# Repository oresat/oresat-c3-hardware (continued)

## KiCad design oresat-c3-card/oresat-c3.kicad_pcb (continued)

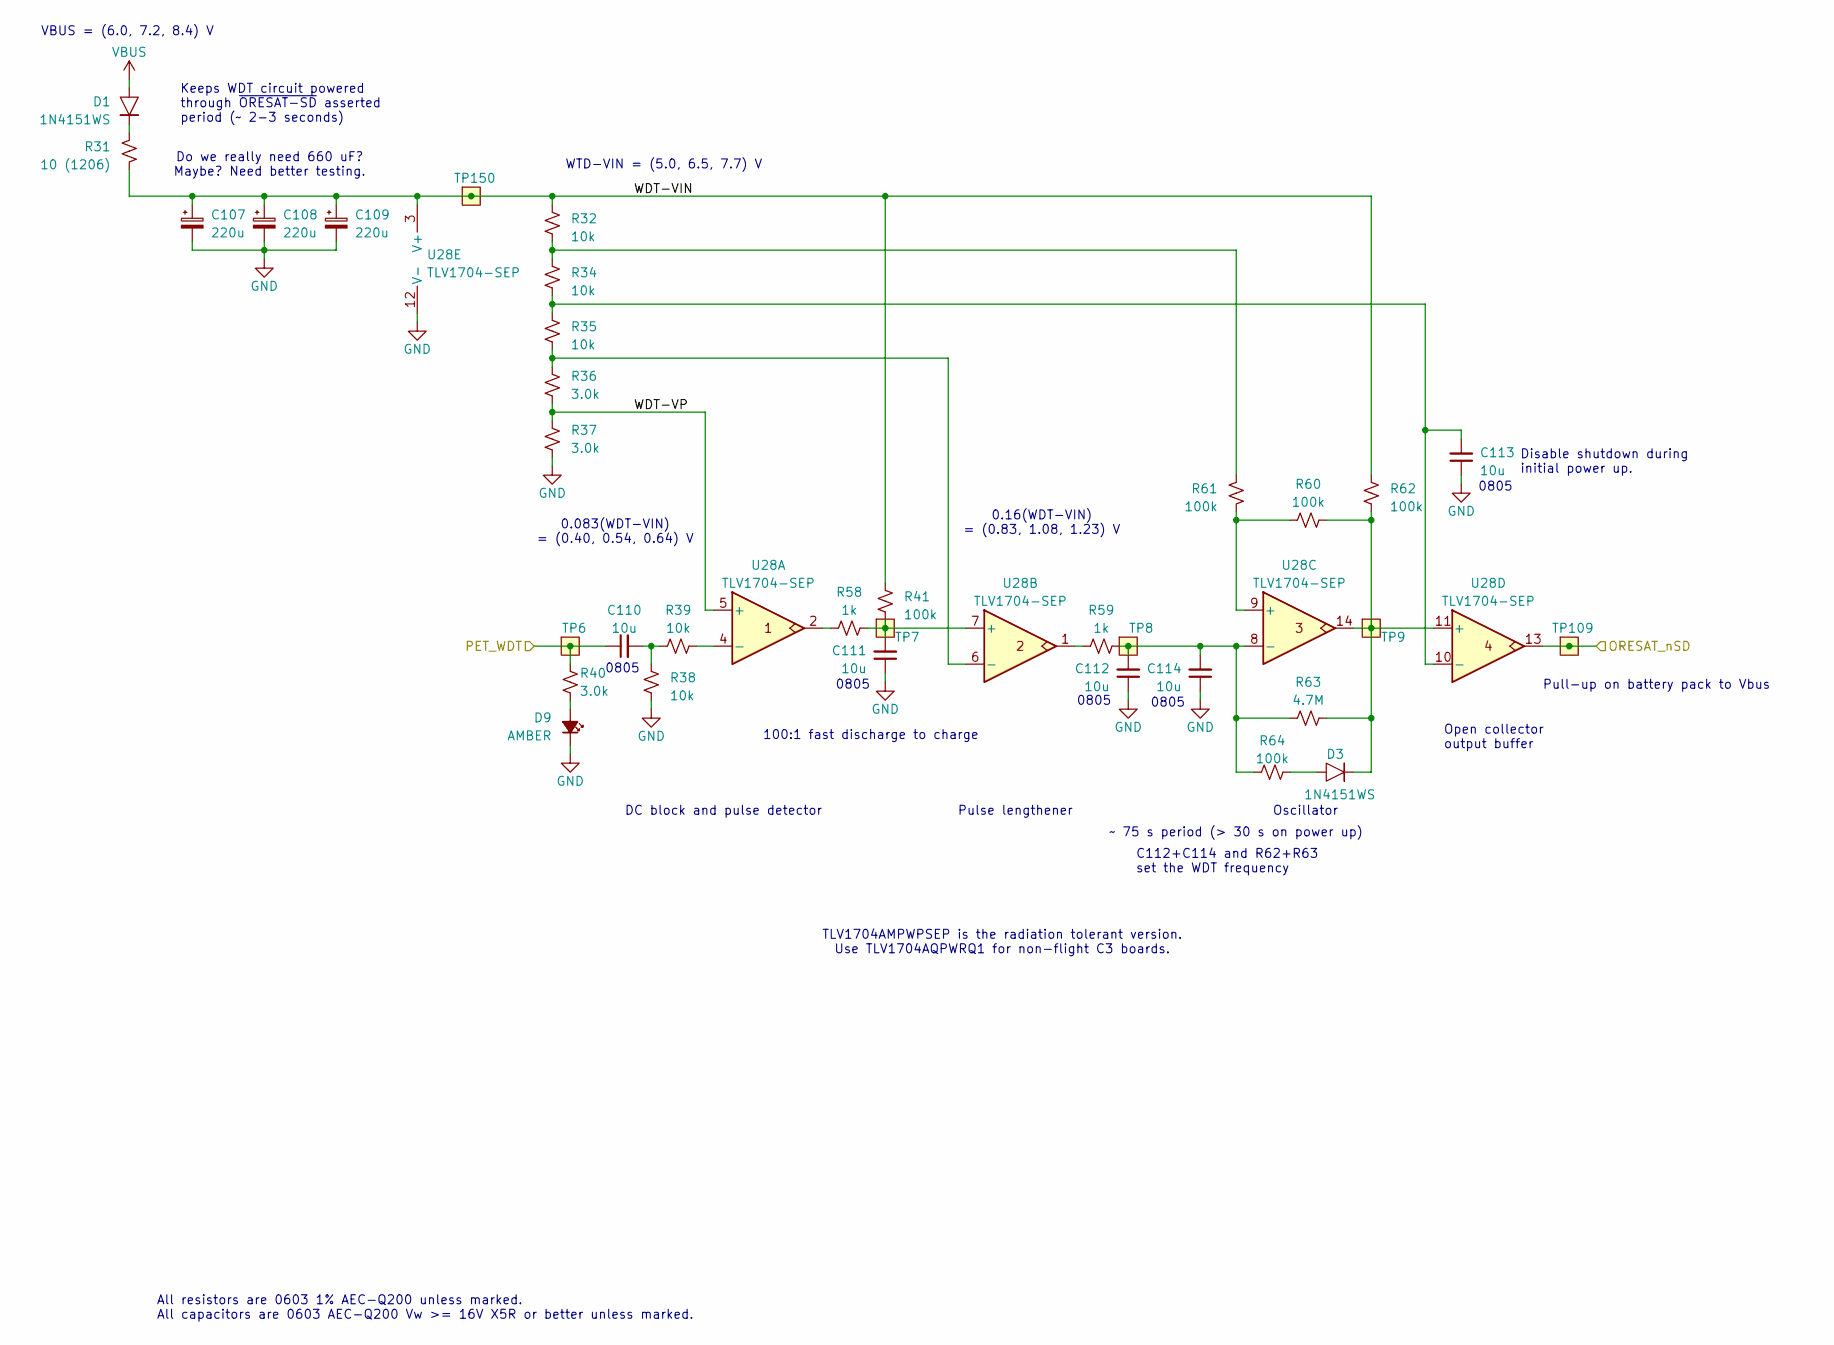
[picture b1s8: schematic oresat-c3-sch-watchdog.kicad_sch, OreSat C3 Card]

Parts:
C107, C108, C109: 220u; CP_EIA-7343-31_Kemet-D; MPN TBJE227K016LBSZ0000
C110, C111, C112, C113, C114: 10u; 0805-C-NOSILK; MPN GRT21BC71E106KE13K
D1, D3: 1N4151WS; D_SOD-323; MPN 1N4151WS-E3-08
D9: AMBER; LED_0603_1608Metric; MPN 150060AS75000
R31: 10 (1206); 1206-C; MPN RMCF1206FT10R0
R32, R34, R35, R38, R39: 10k; 0603-C-NOSILK; MPN RMCF0603FT10K0
R36, R37, R40: 3.0k; 0603-C-NOSILK; MPN RMCF0603FT3K00
R41, R60, R61, R62, R64: 100k; 0603-C-NOSILK; MPN RMCF0603FT100K
R58, R59: 1k; 0603-C-NOSILK; MPN RMCF0603FT1K00
R63: 4.7M; 0603-C-NOSILK; MPN RMCF0603FT4M70
TP6, TP7, TP8, TP9, TP109, TP150: TestPoint-MinTH; TestPoint-0.75mm-th
U28: TLV1704-SEP; TSSOP-14_4.4x5mm_P0.65mm; MPN TLV1704AMPWPSEP

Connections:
/ORESAT_nSD: TP109.1 (1_1), U28.13; also elsewhere on the board
/OSD3358: SIP D/PET_WDT: C110.1, R40.1, TP6.1 (1_1); also elsewhere on the board
/Watchdog/WDT-VIN: C107.1, C108.1, C109.1, R31.2, R32.1, R41.1, R62.2, TP150.1 (1_1), U28.3 (V+)
/Watchdog/WDT-VP: R36.2, R37.1, U28.5 (+)
GND: C107.2, C108.2, C109.2, C111.1, C112.1, C113.1, C114.1, D9.1 (K), R37.2, R38.2, U28.12 (V-); also elsewhere on the board
unnamed: C110.2, R38.1, R39.1
unnamed: D1.1, R31.1
unnamed: D3.2, R64.1
unnamed: D9.2 (A), R40.2
unnamed: R32.2, R34.1, R61.2
unnamed: R58.1, U28.2
unnamed: R59.1, U28.1
unnamed: R39.2, U28.4 (-)
unnamed: C111.2, R41.2, R58.2, TP7.1 (1_1), U28.7 (+)
unnamed: R35.2, R36.1, U28.6 (-)
unnamed: R60.1, R61.1, U28.9 (+)
unnamed: C112.2, C114.2, R59.2, R63.2, R64.2, TP8.1 (1_1), U28.8 (-)
unnamed: D3.1, R60.2, R62.1, R63.1, TP9.1 (1_1), U28.11 (+), U28.14
unnamed: C113.2, R34.2, R35.1, U28.10 (-)
VBUS: D1.2; also elsewhere on the board

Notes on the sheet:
100:1 fast discharge to charge
0805
VBUS = (6.0, 7.2, 8.4) V
Pulse lengthener
Oscillator
C112+C114 and R62+R63 set the WDT frequency
Do we really need 660 uF? Maybe? Need better testing.
WTD-VIN = (5.0, 6.5, 7.7) V
DC block and pulse detector
Open collector output buffer
Pull-up on battery pack to Vbus
0.16(WDT-VIN) = (0.83, 1.08, 1.23) V
All resistors are 0603 1% AEC-Q200 unless marked. All capacitors are 0603 AEC-Q200 Vw >= 16V X5R or better unless marked.
Disable shutdown during initial power up.
Keeps WDT circuit powered through ~{ORESAT-SD} asserted period (~ 2-3 seconds)
TLV1704AMPWPSEP is the radiation tolerant version. Use TLV1704AQPWRQ1 for non-flight C3 boards.
~ 75 s period (> 30 s on power up)
0.083(WDT-VIN) = (0.40, 0.54, 0.64) V

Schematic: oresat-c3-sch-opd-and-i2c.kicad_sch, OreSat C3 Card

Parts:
C79, C129: 1u; 0603-C-NOSILK; MPN GRT188R71E105KE13D
C115: 100u; C_1210_3225Metric; MPN GRT32ER60J107ME13L
C116, C117, C131: 100n; 0603-C-NOSILK; MPN C0603C104K5RACAUTO
D10: 1N4151WS; D_SOD-323; MPN 1N4151WS-E3-08
D12: GREEN; LED_0603_1608Metric; MPN 150060GS75000
Q1: DMP2035UQ-7; SOT-23; MPN DMP2035UQ-7
R49, R51, R66, R78, R79: 10k; 0603-C-NOSILK; MPN RMCF0603FT10K0
R52: 22k; 0603-C-NOSILK; MPN RMCF0603FT22K0
R67: 150; 0603-C-NOSILK; MPN RMCF0603FT150R
R68, R80, R92, R93: 4.7k; 0603-C-NOSILK; MPN RMCF0603FT4K70
TP61, TP141, TP148, TP149, TP160, TP164, TP165, TP166, TP167, TP168, TP169: Test-Point; TestPoint_Pad_D1.0mm
TP163: TestPoint-MinTH; TestPoint-0.75mm-th
U12: RCLAMP0504FB; SOT-363_SC-70-6; MPN RCLAMP0504FBTCT
U13: MAX892LEUA+T; LINEAR-MSOP-8-AND-MAXIM-UMAX-8-21-0036; MPN MAX892LEUA+T
U24: RV-3028-C7; MicroCrystal_C7_SON-8_1.5x3.2mm_P0.9mm; MPN RV-3028-C7 32.768KHZ 1PPM-TA-QA
U30: FM24CL64B-GTR; SOIC-8_3.9x4.9mm_P1.27mm; MPN FM24CL64B-G
U37: LTC4300A-1; LINEAR-MSOP-8-AND-MAXIM-UMAX-8-21-0036; MPN LTC4300A-1IMS8#TRPBF

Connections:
3.3V: C79.1, Q1.2 (S), R49.1, R51.1, U13.1 (IN), U13.2 (IN_2); also elsewhere on the board
/OPD and I2C Peripherals/I2C2_SYS_DISABLE: Q1.1 (G), R66.1; also elsewhere on the board
/OPD and I2C Peripherals/I2C2_SYS_SCL: R80.2, TP168.1 (1_1), U24.3 (SCL), U30.6 (SCL), U37.2 (SCLOUT); also elsewhere on the board
/OPD and I2C Peripherals/I2C2_SYS_SDA: R68.2, TP169.1 (1_1), U24.4 (SDA), U30.5 (SDA), U37.7 (SDAOUT); also elsewhere on the board
/OPD and I2C Peripherals/OPD_CURRENT: R52.1, TP61.1 (1_1), U13.5 (SET); also elsewhere on the board
/OPD and I2C Peripherals/OPD_nENABLE: R49.2, TP167.1 (1_1), U13.3 (~ON); also elsewhere on the board
/OPD and I2C Peripherals/OPD_nFAULT: R51.2, TP166.1 (1_1), U13.6 (~FAULT); also elsewhere on the board
/OPD_PWR: C129.1, C131.1, R78.2, R92.1, R93.1, TP163.1 (1_1), U12.5 (VCC), U13.7 (OUT_2), U13.8 (OUT), U37.1 (ENABLE), U37.8 (VCC); also elsewhere on the board
/OPD_SCL: R92.2, TP164.1 (1_1), U12.1 (I1), U37.3 (SCLIN); also elsewhere on the board
/OPD_SDA: R93.2, TP165.1 (1_1), U12.3 (I2), U37.6 (SDAIN); also elsewhere on the board
GND: C79.2, C115.2, C116.2, C117.2, C129.2, C131.2, D12.1 (K), R52.2, R66.2, R79.2, U12.2 (GND), U13.4 (GND), U24.5 (VSS), U30.1 (A0), U30.2 (A1), U30.3 (A2), U30.4 (VSS), U37.4 (GND); also elsewhere on the board
unnamed: D10.2, R67.2
unnamed: D12.2 (A), R78.1
unnamed: C116.1, C117.1, Q1.3 (D), R67.1, R68.1, R80.1, U24.7 (VDD), U30.8 (VDD)
unnamed: TP141.1 (1_1), U24.1 (CLKO)
unnamed: R79.1, TP149.1 (1_1), U24.8 (EVI)
unnamed: C115.1, D10.1, U24.6 (VBKP)
unnamed: TP148.1 (1_1), U24.2 (~INT)
unnamed: TP160.1 (1_1), U30.7 (WP)

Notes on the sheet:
To OPD. See Connectors sheet.
Should not go above 1.4V
8k x 8 (64kb) I2C FRAM
FRAM
All resistors are 0603 1% AEC-Q200 unless marked. All capacitors are 0603 AEC-Q200 Vw >= 16V X5R or better unless marked.
Normally on; asserting I2C_SYS_DISABLE will turn off this subsystem.
IMPORTANT: To power down RTC/FRAM, OPD_PWR must be turned off as well to prevent pullup voltage bleeding through the LTC4300A-1.
Limits OPD_PWR to 54 mA
I2C pullups provided by RTC/FRAM power PFET above.
Murata GRT32ER60J107ME13L 100uF 20% 6.3V X5R 1210 Capacitor
1210
HOW LONG WILL IT KEEP?
RTC
OreSat Power Domain (OPD) Control

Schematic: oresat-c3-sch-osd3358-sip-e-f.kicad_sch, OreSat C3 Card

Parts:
TP19, TP20, TP21, TP22: Test-Point; TestPoint_Pad_D1.0mm
U1: OSD3358-1G-ISM; U-Octavo-OSD335X-BGA-256; MPN OSD3358-512M-BSM

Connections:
GND: U1.D8 (DGND@1), U1.D9 (DGND@2), U1.E5 (DGND@3), U1.E6 (DGND@4), U1.E7 (DGND@5), U1.E8 (DGND@6), U1.E9 (DGND@7), U1.E10 (DGND@8), U1.E11 (DGND@9), U1.E12 (DGND@10), U1.F5 (DGND@11), U1.F12 (DGND@12), U1.G5 (DGND@13), U1.G12 (DGND@14), U1.H4 (DGND@15), U1.H5 (DGND@16), U1.H12 (DGND@17), U1.H13 (DGND@18), U1.J4 (DGND@19), U1.J5 (DGND@20), U1.J12 (DGND@21), U1.J13 (DGND@22), U1.K5 (DGND@23), U1.K12 (DGND@24), U1.L5 (DGND@25), U1.L12 (DGND@26), U1.M5 (DGND@27), U1.M6 (DGND@28), U1.M7 (DGND@29), U1.M8 (DGND@30), U1.M9 (DGND@31), U1.M10 (DGND@32), U1.M11 (DGND@33), U1.M12 (DGND@34), U1.N8 (DGND@35), U1.N9 (DGND@36); also elsewhere on the board
unnamed: TP19.1 (1_1), U1.F4 (VDDS_DDR)
unnamed: TP22.1 (1_1), U1.G13 (VDDS_PLL)
unnamed: TP20.1 (1_1), U1.G4 (VDD_CORE)
unnamed: TP21.1 (1_1), U1.F13 (VDD_MPU)

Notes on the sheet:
All resistors are 0603 1% AEC-Q200 unless marked. All capacitors are 0603 AEC-Q200 Vw >= 16V X5R or better unless marked.

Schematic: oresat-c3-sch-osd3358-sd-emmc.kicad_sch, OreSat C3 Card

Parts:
C16, C25: 10u; 0805-C-NOSILK; MPN GRT21BC71E106KE13K
C17, C18, C48: 100n; 0603-C-NOSILK; MPN C0603C104K5RACAUTO
C19, C20, C21, C22, C23, C24: 1u; 0603-C-NOSILK; MPN GRT188R71E105KE13D
D4, D5, D6, D7: BLUE; LED_0603_1608Metric; MPN 150060BS75000
J5: DM3BT-DSF-PEJS; J-Hirose-DM3BT-DSF-PEJS; MPN DM3BT-DSF-PEJS
R30, R42, R43, R44, R45, R90: 10k; 0603-C-NOSILK; MPN RMCF0603FT10K0
R69, R70, R71: 10k; Panasonic_Resistor_Array_EXBA10; MPN EXB-A10P103J
R91, R94: 150; 0603-C-NOSILK; MPN RMCF0603FT150R
TP27, TP33, TP34, TP35, TP38, TP39, TP42, TP46, TP47, TP48, TP64, TP65, TP66, TP68, TP89, TP124, TP126, TP162, TP170: Test-Point; TestPoint_Pad_D1.0mm
U1: OSD3358-1G-ISM; U-Octavo-OSD335X-BGA-256; MPN OSD3358-512M-BSM
U8: TCAN330; SOT-23-8; MPN TCAN330GDCNT
U9: SFEM016GB1EA1TO-I-GE-121-STD; BGA-153(11.5X13)(EMMC-BA); MPN SFEM064GB2ED1TO-A-6F-111-STD
U42: 74LVC2G34; SOT-363_SC-70-6; MPN 74LVC2G34GW-Q100,1

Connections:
3.3V: C16.1, C17.1, C18.1, C21.1, C22.1, C23.1, C24.1, C25.1, C48.2, J5.4 (VDD), R69.5 (55), R69.10 (55), R70.5 (55), R70.10 (55), R71.5 (55), R71.10 (55), U8.3 (VCC), U9.C6 (VDDQ), U9.E6 (VDDIO), U9.F5 (VDDIO), U9.J10 (VDDIO), U9.K9 (VDDIO), U9.M4 (VDDQ), U9.N4 (VDDQ), U9.P3 (VDDQ), U9.P5 (VDDQ), U42.5 (VCC); also elsewhere on the board
/C3-UART-RX: U1.A12 (UART0_RXD); also elsewhere on the board
/C3-UART-TX: U1.B12 (UART0_TXD); also elsewhere on the board
/CAN1_H: U8.7 (CANH); also elsewhere on the board
/CAN1_L: U8.6 (CANL); also elsewhere on the board
/L Band/LBAND_IRQ: U1.R16 (GPMC_WPN); also elsewhere on the board
/L Band/SPI1_CS: U1.A4 (XDMA_EVENT_INTR0); also elsewhere on the board
/L Band/SPI1_MISO: U1.C12 (UART0_CTSN); also elsewhere on the board
/L Band/SPI1_MOSI: U1.C13 (UART0_RTSN); also elsewhere on the board
/L Band/SPI1_SCLK: U1.C5 (ECAP0_IN_PWM0_OUT); also elsewhere on the board
/OPD and I2C Peripherals/I2C2_SYS_DISABLE: U1.R6 (GPMC_AD13); also elsewhere on the board
/OPD and I2C Peripherals/I2C2_SYS_SCL: U1.A10 (UART1_RTSN); also elsewhere on the board
/OPD and I2C Peripherals/I2C2_SYS_SDA: U1.B10 (UART1_CTSN); also elsewhere on the board
/OPD and I2C Peripherals/OPD_nENABLE: U1.C3 (MCASP0_AXR1); also elsewhere on the board
/OPD and I2C Peripherals/OPD_nFAULT: U1.B3 (MCASP0_FSR); also elsewhere on the board
/OSD3358: SIP C/CAN1_RXD: U1.B11 (UART1_TXD), U8.4 (RXD)
/OSD3358: SIP C/CAN1_TXD: U1.A11 (UART1_RXD), U8.1 (TXD)
/OSD3358: SIP C/EMMC_CMD: R70.2 (22), U1.P1 (GPMC_CSN2), U9.M5 (CMD)
/OSD3358: SIP C/EMMC_D0: R70.6 (66), U1.R3 (GPMC_AD0), U9.A3 (D0)
/OSD3358: SIP C/EMMC_D1: R71.1 (11), U1.R2 (GPMC_AD1), U9.A4 (D1)
/OSD3358: SIP C/EMMC_D2: R71.9 (99), U1.R1 (GPMC_AD2), U9.A5 (D2)
/OSD3358: SIP C/EMMC_D3: R70.7 (77), U1.T3 (GPMC_AD3), U9.B2 (D3)
/OSD3358: SIP C/EMMC_D4: R70.4 (44), U1.T2 (GPMC_AD4), U9.B3 (D4)
/OSD3358: SIP C/EMMC_D5: R70.3 (33), U1.T1 (GPMC_AD5), U9.B4 (D5)
/OSD3358: SIP C/EMMC_D6: R71.8 (88), U1.P4 (GPMC_AD6), U9.B5 (D6)
/OSD3358: SIP C/EMMC_D7: R71.2 (22), U1.R4 (GPMC_AD7), U9.B6 (D7)
/OSD3358: SIP C/EMMC_SCK: R70.8 (88), U1.P2 (GPMC_CSN1), U9.M6 (SCK)
/OSD3358: SIP C/EMMC_nRST: R71.3 (33), U1.R13 (GPMC_A4), U9.K5 (~RST)
/OSD3358: SIP C/L_BAND_ENABLE: U1.T13 (GPMC_A3); also elsewhere on the board
/OSD3358: SIP C/MMC1_CD: J5.CD (CD#), R69.6 (66), U1.C14 (SPI0_CS1)
/OSD3358: SIP C/MMC1_CLK: J5.5 (CLK), R69.3 (33), U1.B15 (MMC0_CLK)
/OSD3358: SIP C/MMC1_CMD: J5.3 (CMD/DI), R69.8 (88), U1.B16 (MMC0_CMD)
/OSD3358: SIP C/MMC1_DAT0: J5.7 (DAT0/DO), R69.9 (99), U1.A16 (MMC0_DAT0)
/OSD3358: SIP C/MMC1_DAT1: J5.8 (DAT1), R69.4 (44), U1.A15 (MMC0_DAT1)
/OSD3358: SIP C/MMC1_DAT2: J5.1 (DAT2), R69.7 (77), U1.C16 (MMC0_DAT2)
/OSD3358: SIP C/MMC1_DAT3: J5.2 (DAT3/CS), R69.2 (22), U1.C15 (MMC0_DAT3)
/OSD3358: SIP C/PIN7-GPIO: R30.2, U1.B2 (MCASP0_AXR0), U42.3
/OSD3358: SIP C/PIN8-GPIO: R90.2, U1.A1 (MCASP0_ACLKX), U42.1
/OSD3358: SIP C/RADIO_nFLT: U1.A3 (MCASP0_ACLKR); also elsewhere on the board
/OSD3358: SIP C/SPI0_CS: U1.A14 (SPI0_CS0); also elsewhere on the board
/OSD3358: SIP C/SPI0_MISO: U1.B13 (SPI0_D0); also elsewhere on the board
/OSD3358: SIP C/SPI0_MOSI: U1.B14 (SPI0_D1); also elsewhere on the board
/OSD3358: SIP C/SPI0_SCLK: U1.A13 (SPI0_SCLK); also elsewhere on the board
/OSD3358: SIP C/UHF_ENABLE: U1.T12 (GPMC_A0); also elsewhere on the board
/OSD3358: SIP C/UHF_IRQ: U1.P15 (GPMC_WAIT0); also elsewhere on the board
/OSD3358: SIP C/UHF_PA_ENABLE: U1.T16 (GPMC_A11); also elsewhere on the board
/OSD3358: SIP C/UHF_TOT_CLEAR: U1.R15 (GPMC_A10); also elsewhere on the board
/OSD3358: SIP C/UHF_TOT_OK: U1.T15 (GPMC_A9); also elsewhere on the board
/OSD3358: SIP C/USR1: R42.1, U1.P13 (GPMC_A5)
/OSD3358: SIP C/USR2: R43.1, U1.T14 (GPMC_A6)
/OSD3358: SIP C/USR3: R44.1, U1.R14 (GPMC_A7)
/OSD3358: SIP C/USR4: R45.1, U1.P14 (GPMC_A8)
/PIN7-OUT: R94.1; also elsewhere on the board
/PIN8-OUT: R91.1; also elsewhere on the board
GND: C16.2, C17.2, C18.2, C19.2, C20.2, C21.2, C22.2, C23.2, C24.2, C25.2, C48.1, D4.1 (K), D5.1 (K), D6.1 (K), D7.1 (K), J5.6 (VSS), J5.CGND1 (CGND), J5.CGND2 (CGND), J5.CGND3 (CGND), J5.CGND4 (CGND), J5.CGND5 (CGND), J5.CGND6 (CGND), J5.GND (VSS), R30.1, R90.1, U8.2 (GND), U9.A6 (VSSIO), U9.C4 (VSSQ), U9.E7 (VSSIO), U9.G5 (VSSIO), U9.H10 (VSSIO), U9.J5 (VSSIO), U9.K8 (VSSIO), U9.N2 (VSSQ), U9.N5 (VSSQ), U9.P4 (VSSQ), U9.P6 (VSSQ), U42.2 (GND); also elsewhere on the board
unnamed: D4.2 (A), R42.2
unnamed: D5.2 (A), R43.2
unnamed: D6.2 (A), R44.2
unnamed: D7.2 (A), R45.2
unnamed: R91.2, U42.6
unnamed: R94.2, U42.4
unnamed: TP38.1 (1_1), U1.R12 (GPMC_A1)
unnamed: TP39.1 (1_1), U1.P12 (GPMC_A2)
unnamed: TP170.1 (1_1), U1.T4 (GPMC_AD8)
unnamed: TP162.1 (1_1), U1.P5 (GPMC_AD9)
unnamed: TP126.1 (1_1), U1.R5 (GPMC_AD10)
unnamed: TP124.1 (1_1), U1.T5 (GPMC_AD11)
unnamed: TP89.1 (1_1), U1.P6 (GPMC_AD12)
unnamed: TP42.1 (1_1), U1.T6 (GPMC_AD14)
unnamed: TP46.1 (1_1), U1.P7 (GPMC_AD15)
unnamed: TP64.1 (1_1), U1.N3 (GPMC_BEN0_CLE)
unnamed: TP68.1 (1_1), U1.T7 (GPMC_CLK)
unnamed: TP47.1 (1_1), U1.P3 (GPMC_CSN0)
unnamed: TP48.1 (1_1), U1.R7 (GPMC_CSN3)
unnamed: TP66.1 (1_1), U1.N1 (GPMC_OEN_REN)
unnamed: TP65.1 (1_1), U1.N2 (GPMC_WEN)
unnamed: TP33.1 (1_1), U1.B1 (MCASP0_AHCLKR)
unnamed: TP34.1 (1_1), U1.C4 (MCASP0_AHCLKX)
unnamed: TP27.1 (1_1), U1.A2 (MCASP0_FSX)
unnamed: TP35.1 (1_1), U1.B4 (XDMA_EVENT_INTR1)
unnamed: C19.1, C20.1, U9.C2 (VDDI)

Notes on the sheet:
0805
TO L BAND RADIO
eMMC Flash Memory
GPIO to the backplane for controlling various peripherals (e.g., ESI's S Band Radio) on pins SPARE7 and SPARE8.
Removable uSD Card
Need ~2.2uF, using two 1uF for simplicity
TO L RADIO
SIP pin states ("ZZ", "LL", "ZL", etc) are GPIO states of the pin during and immediately after a reset. See Pg 18-47 in https://www.ti.com/lit/ds/symlink/am3358.pdf
USR LEDs
Z[L|0|CLK]
TO C3 I2C Peripherals
16 GB (128 Gb) eMMC
(Clear this area on schematic sheet for eMMC unconnected pin array)
All resistors are 0603 1% AEC-Q200 unless marked. All capacitors are 0603 AEC-Q200 Vw >= 16V X5R or better unless marked.
CAN Transceiver
TO UHF RADIO

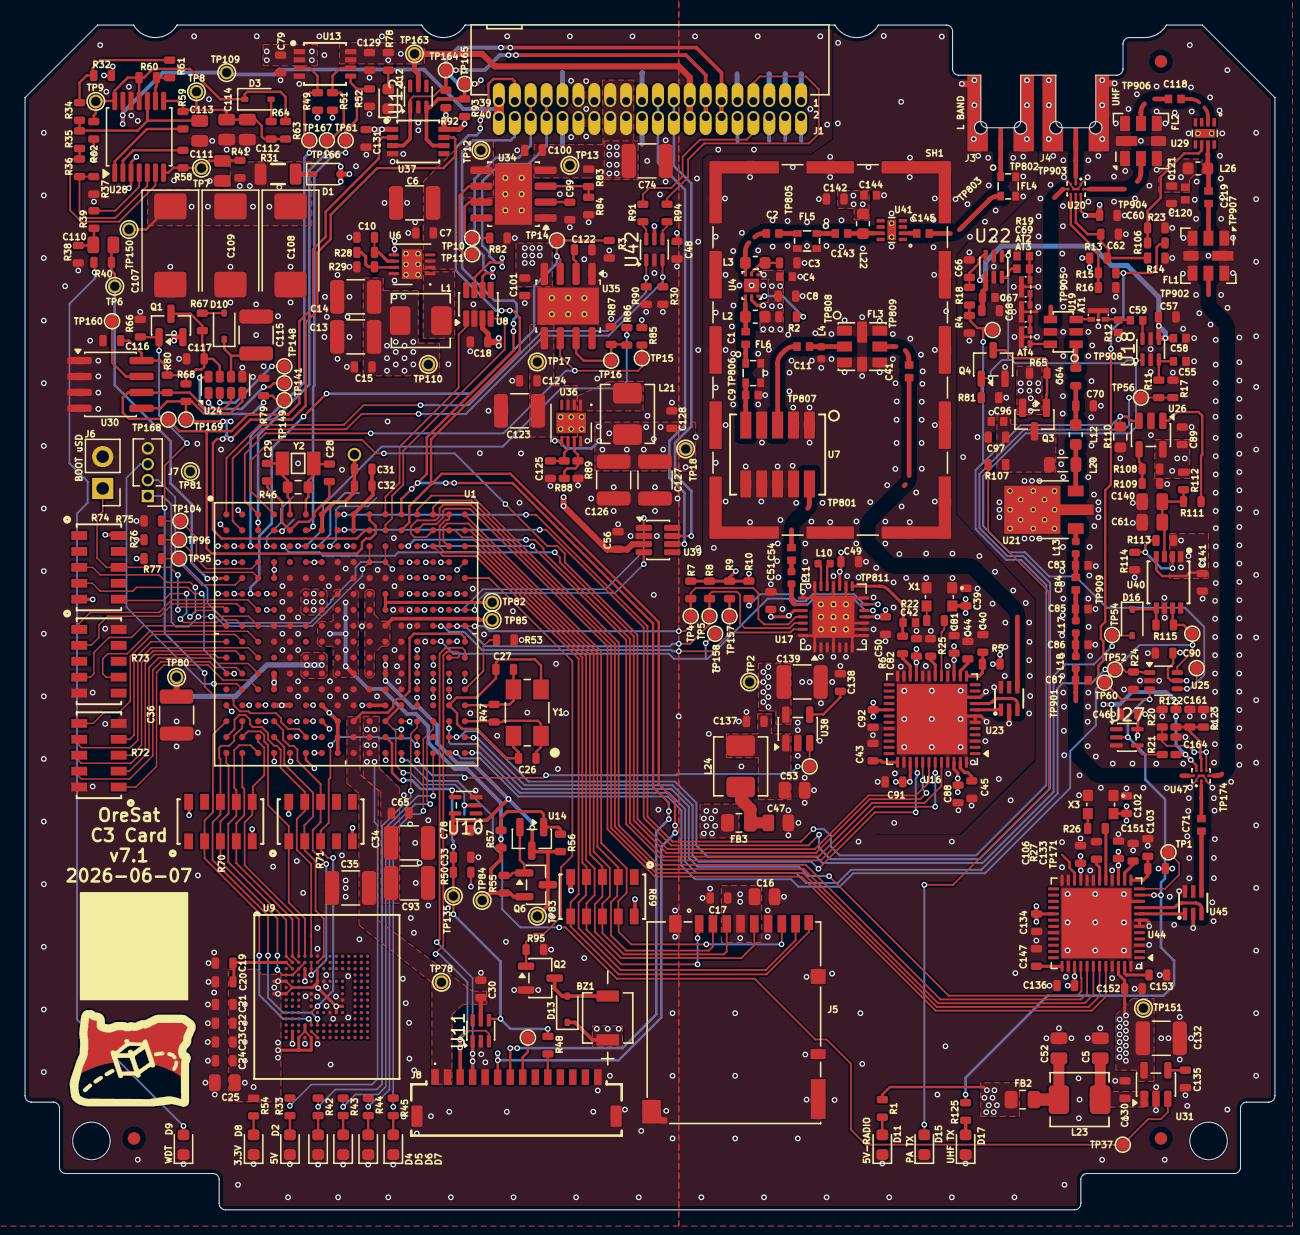
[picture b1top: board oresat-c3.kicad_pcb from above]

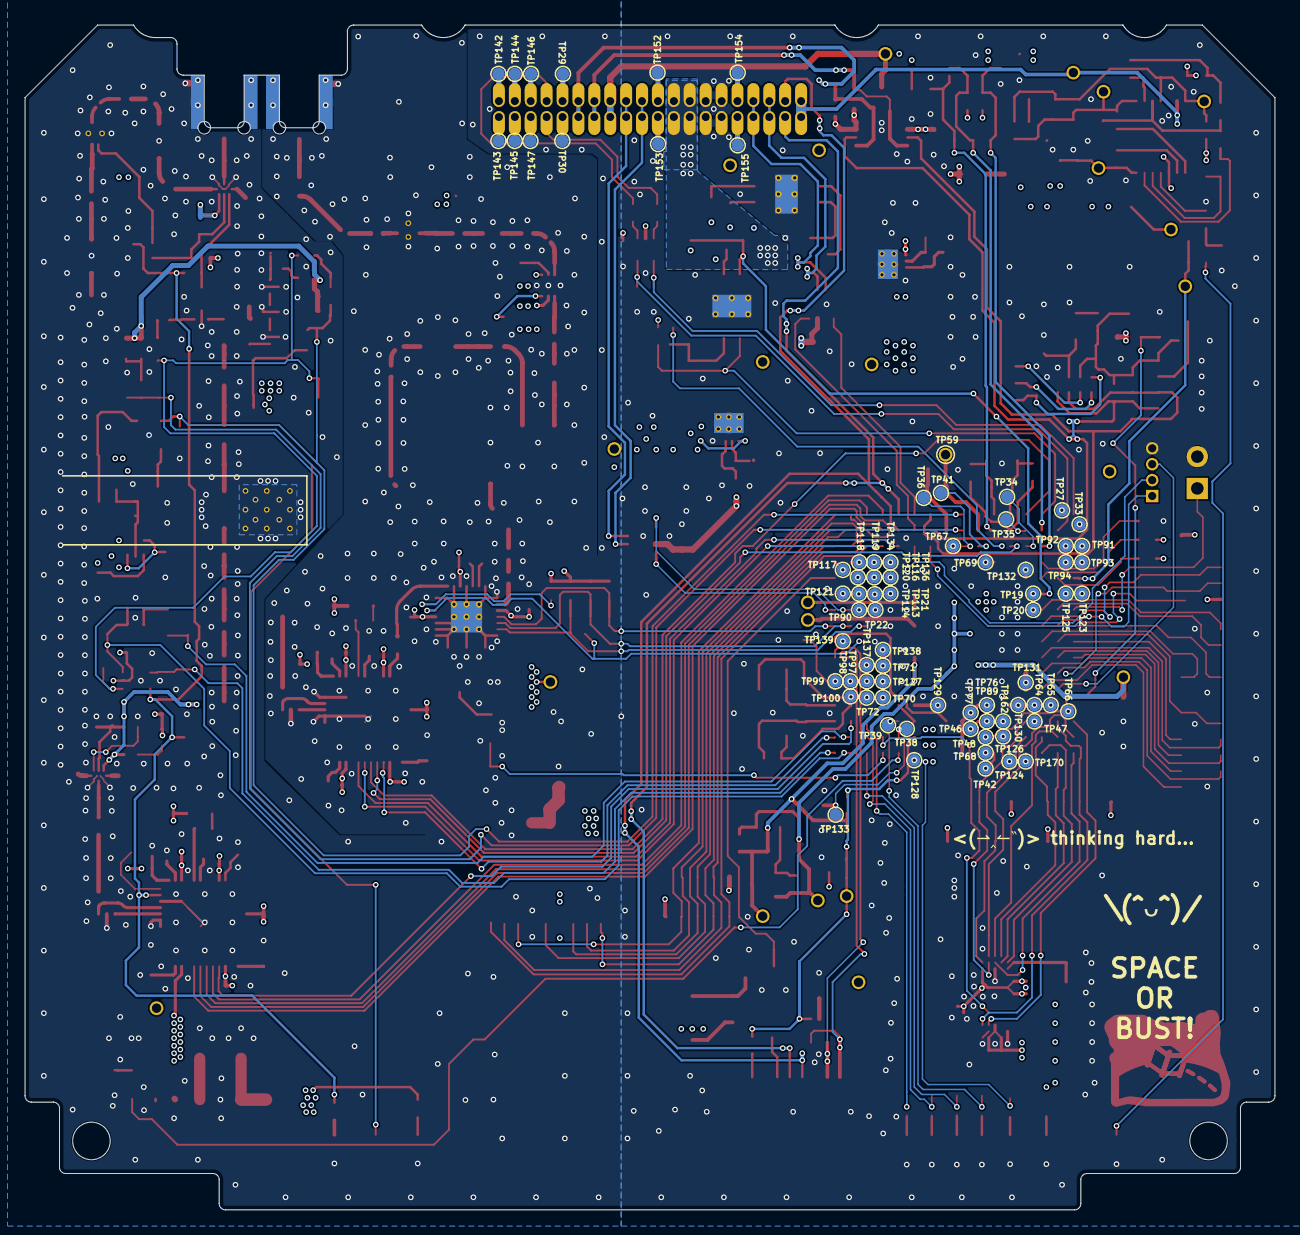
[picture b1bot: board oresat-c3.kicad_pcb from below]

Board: 4 copper layers, 99.8 x 94.6 mm, 504 parts (76 on the bottom side), 342 nets.

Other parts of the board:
LOGO: logo-small

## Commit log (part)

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2019-10-17 Started some simple documentation
2019-10-18 Added device proposal as per Practicum requirements
2019-10-30 Initial commit of V3 protocard based C3 prototype
2019-10-31 adding videos
2019-11-02 MPP File
    Updated 2 tasks to add.
2019-11-06 Most F4 nets labelled. Connected to OPD CB.
2019-11-07 connected CAN bus chips
2019-11-07 Update Gantt .mpp file and pdf
    Added names to tasks on .mpp file. Removed Gantt_2.pdf, replaced with updated Gantt_1.pdf. Never needed a Gantt_2 to begin with.
2019-11-07 Cleaning up board layout
2019-11-07 Added OPD and CAN2 connector
2019-11-14 layed out most of the board awaiting review and adding BOM
2019-11-14 Routed spare pins to header and a little cleanup
2019-11-15 Fixed VBUSP routing around the SPS
2019-11-17 Added the Radio breakout board schematic and layout to the eagle folder under DVK2C-breakout.sch
2019-11-18 adding it back
2019-11-19 Added radio pins, added supply pin capacitors, moved some components
2019-11-20 made some connections
2019-11-21 added MCU test points
2019-11-21 cleaned up a little bit, connected last few routes
2019-11-21 Fixed some DRC errors
2019-11-21 passed DRC
2019-11-21 Added TP for one last MCU pin
2019-11-24 Fix VCAP, fix JTAG header, remove weird 0.1in headers which make SPI bus go everywhere, fix component tyes, add test points, polish.
2019-11-25 Replaced new ICs with versions in the oresat-eagle-libraries repo
2019-11-26 Added the BOM for the practicum C3 board
2019-12-07 added the XTAL data sheet
2019-12-12 Adding some documentation links
2020-01-19 Note for replacing SD card with eMMC
    hand written eMMC notes
2020-01-20 Added eMMC
    Almost completed adding eMMC
2020-01-21 Make changes to oresat-c3-v1 board
    Fix eMMC pin out to better match datasheet
    Route data lines to match lengths
2020-01-22 implemented changes after design Review with Andrew
2020-01-22 Updated eMMC Notes
2020-01-23 Housekeeping
    Put homeworks from Fall 2019 Practicum into their own folder.
2020-01-24 Made Design review changes to C3 board
    updated changes made in design review doc
2020-01-24 Replace lost wire
2020-01-25 Fix some connections
2020-01-25 Changed pads and via layout under RF
2020-01-31 A wee bit of polish to get it off to OSH Park. v1 sent to fab.
2020-01-31 version 2 created
2020-02-06 Parts Move so far
    not completed
2020-02-14 Create vSupUT01VS33D - Cobham Voltage Supervisor.pdf
    Added voltage supervisor datasheet.
2020-02-17 Work in progress
    Moving and making room for radio
2020-02-18 Updated Layout Notes
    updated eMMC notes and added move notes for making room for split plane
2020-02-20 Removed jumper Fixed DRC errors
2020-02-21 Minor adjustments
    Minor adjustments to edge connector and labeling, shifted some of the Watchdog circuit
2020-02-23 Added TVS Diode Datasheet
    OPD Protection Circuit TVS Diode Datasheet.
2020-02-29 put in segregated ground planes, added the version of the project proposal that was signed to the docs folder
2020-03-03 Added TVS diodes for watchdog and OPD
2020-03-06 Added a design blocks folder for RF integration
2020-03-06 Added UDH power tree dbl
2020-03-07 Allocated MCU pins for deployment system, sythnesizer control, and feedback. Added initial deployment circuitry.
2020-03-07 Changes made to the watchdog
2020-03-08 Connected UHF/ UHF Power Tree (mostly)
2020-03-09 Edit WDT Symbol and Removed TVS on SD line
    Moved WDI onto left side of WDT symbol. Removed U8 (TVS Diodes connected to SD line)
2020-03-15 Making room for when we change MCU
2020-03-16 completed making room for new MCU
    Made many design review changes
    removed all temp save files
2020-03-17 swapped the L-band and UHF areas
2020-03-20 Replaced parts form tova library with their own library components
2020-03-22 Made changes after Vigely's L Band review
2020-03-22 Fixed U17
2020-03-23 Added Supplys after Zero ohm resistors for 3.3V sources
2020-03-24 Design review changes
    L-band 2.5V LDO bypass 10n
    Use same LDO for UHF 3.3V Lp2985
    Put 1% on resistor note.
    Put working voltage on caps note.
    Run A MASSIVE trave From the 5V SPS to the UHF
    Break up the pad on tcream layer under the power pads for the solder stencils
2020-03-25 DRC clean up , Fixed small Test Points
2020-03-25 Added 100k pull up resistors on the LDO's
2020-03-26 more desing review changes
2020-03-26 Removed more Airwires
2020-03-27 Rerouted the VBUS from edge connector
2020-03-27 added some test points and 0 ohms to UHF RF path
2020-03-30 Finished adding test pads and 0hms to the L band RF path
2020-04-02 Added WDT band-aide
2020-04-10 updated some testpoints
2020-04-10 Fixed Airwires; wire stubs Approved warnings
2020-04-14 retired some 04/12 design review items
2020-04-14 Final design rule changes Made
2020-04-16 v2 OFF TO FABgit status Lots of cleanup on TNAMEs, cleanup on solder mask openings for microstrips, a bit of power rework near AX5043s. TODO: Make all 0603 components the smaller C version, which can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
2020-04-28 Edited Attributes
2020-04-28 Finished adding UHF part attributes for BOM generation
2020-04-29 Fix Sync Error
2020-05-14 Move some BOM files
2020-05-17 Connecting in new 100 pin Microprocessor
2020-05-17 Made Sure Resistor values are shown on schematic
2020-06-11 Re push Changes made to watchdog and Antenna deplayment
2020-06-11 Changed capacitors for the watchdog
2020-06-26 Minor cleanup and clearing ERC and DRC
2020-06-26 Clean up Libraries, Worked on BOM for V3
2020-06-29 Change text dimensions
2020-07-20 Tried to fix EAGLE errors for OSH Park; failed, we need to make Gerbers for them.
2020-07-28 Added part attributes for the dual pch mosfets
2020-08-18 Added PA design block , Replaced u Processor, Fixed/replaced X1 crystal
2020-08-23 Added updated UHF PA design block
2020-08-23 Moved UHF PA to UHF Sheet
2020-08-26 Added tstop and Power to UHF PA
2020-08-28 design information added for PA UHF
2020-09-18 Added TOT schematic for UHF
2020-10-13 minor clean up of schematic and added split planes back in for radios
2020-12-14 UHF section: rough draft done. Moved 5V SPS closer to PA, shifted over 0.1 connector, revamped the time-out-timer (TOT) to be way smaller and use the right logic in smaller packages. Moved the whole 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
2020-12-31 Giant massage of parts to get more room for RTCs, and put some room between modular blocks.
2021-01-02 UHF section review and polish done. L Band 50% done. Then TNAME, and .. done?
2021-01-03 Added FRAM, because FRAMgit add oresat-c3.brd oresat-c3.sch, added 5th order LPF for UHF TX. Waiting on final values of LPF and time out timer (TOT) from Glenn, then need to fix attributes and ship!
2021-01-04 Fixed up PA TSTOP and TCREAM, fixed quad nchannel TCREAM, added call signs of main C3 folks, fixed 2mm miter on RF lines.
2021-02-07 Changes to the timeout timer based on available parts; updated SCH and BOM. Also fixed off-by-one-row errors for Mouser parts.
2021-02-07 Updated to the CERN-OHL-S v2!
2021-02-14 Fixed swap of pins 2 and 3 on the TOT; renamed TOT pins to be better names (TOT_OUT is now !TOT_PA_DISABLE).
2021-02-16 Fixed some DRC issues.
2021-03-08 Updated TOT values to make it 1 second long. Added "RF test points" and some associated ground points with level values to help future debugging.
    UGH: in previous commit, forgot to mention the most important fixes:
    - Fixed TOT swap of pin 2,3 and the non-working functionality of the !SHDN. M4 now unlatches output only, and does not affect output of the circuit.
    - Fixed WDT with latest "Tim" version (thanks Tim!) with small changes to values to operate correctly.
2021-03-08 Minor polishing with Glenn, removed L band TX components, fixed BOM.
2022-10-09 Added KiCad C3 import
2022-12-29 Switched to v2 backplane connector, removed GPS RF.
2022-12-30 Fixes #39 - added ILIM to ADC on PA3 via 10K resistor.
2022-12-30 Fixes #40 - more capacitance on 3.3V SPS in and out to help with brownouts.
2023-03-16 Converted kicad directory over to our latest Octavo-based v6 design starting from the GPS card.
2023-04-16 Started moving RF schematic bits over to KiCad
2023-05-03 Rough draft of watchdog and I2C system schematics.
2023-05-05 Simulated 30 second v6 watchdog circuit and fixed up watchdog in KiCAD.
2023-05-31 Big cleanup on UHF radio; about 50% done.
2023-06-01 Flipped UHF schematic to be L to R, more polish, added direction arrows. Started on L band radio. Added latest oresat-kicad libraries, started to remove old libraries (e.g., GPS).
2023-06-02 Sane amount of ERC errors now; mostly library cleanups.
2023-06-03 Updated all footprints for sheet one of the schematic.
2023-06-04 working on power sheet.
2023-06-08 Updated test points, fixed some more hidden ERCs.
2023-06-22 Fixed footprints and laid out WDT and OPD circuitry.
2023-06-23 Moved octavo and emmc over radio. It's going to be tight, but it looks doable. started L band layout.
2023-06-26 More radio cleanup!
2023-06-29 Rough draft of L band radio complete; committing in order to start really screwing around with ground planes.
2023-06-29 Zero airwires! Rough draft schematic and layout are done. Still need ERC and DRC and full design review and stiching and polish.
2023-07-05 More DRC cleanup. Now below 400.
2023-08-24 More polish; fixed all non-RF DRCs.
2023-08-27 Ryan made me do it: added CAN0 tranceiver.
2023-08-28 First round of BOM fixes and optimizations.
2023-08-29 ignore build directories
2023-09-04 Fixed part name, removed solder mask from the back of some of the library components for venting.
2023-11-01 Add expected dBm values on radio TX and RXs.
2023-11-19 Real part numbers for FB parts, routed signals for the UHF_ENABLE AND L_BAND_ENABLE signals.
2024-01-05 Minor DRC changes
2024-03-18 Fixed Q1 in the I2C subsystem, which was backward but we never noticed. Removed hardware ID resistors and added back in test points, since HW ID is now stored in internal EEPROM. Updated power measur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
2024-04-01 OOof, almost ordered with incorrect RF netclass. Reset to 0.5 mm keepouts.
2024-04-09 Updated readme!
2025-11-11 added and rerouted new debug connector, added a few test points
2025-12-28 Removed old EAGLE files, renamed kicad directory to the card directory.
2026-02-02 Replaced AX5043 for UHF and added TX/RX switch control
2026-02-02 started routing UHF and L band chip replacement on PCB
2026-02-18 schematic changes following design review
2026-02-21 More progress on schematic from design review, routed new debug connector and updated balun routing
2026-03-04 Design review on power and RF
2026-03-08 added mask on RF traces and fixed UHF power routing
2026-03-15 Routing complete; on to cleanup!
2026-03-16 UHF optimized. Ready for polishing
2026-03-17 All footprints updated. Passes ERC/DRC.
2026-03-18 Clean up local directory - remove old cruft from schematic and old EAGLE import libraries
2026-03-18 Fix a bunch of 3D models
2026-03-19 Upgrade makefile to create README.pdf using pandoc and sed. Polish up README.md to be more consistant and emphasize IPC-2581.
2026-03-19 Fixed some RF DRC errors, and then added two custom rules to get rid of the pesky RF errors which leaves us with ZERO DRC errorsgit add .!
2026-03-22 Changed WDT tantalums to space-rated tantalums (fun) and fixed some BOM issues. Also possibly more silk screen cleanup.
2026-04-01 BOM only change: Upgraded single gate inverter to AEC qualified version
2026-04-21 Update .gitignore to kicad 10
